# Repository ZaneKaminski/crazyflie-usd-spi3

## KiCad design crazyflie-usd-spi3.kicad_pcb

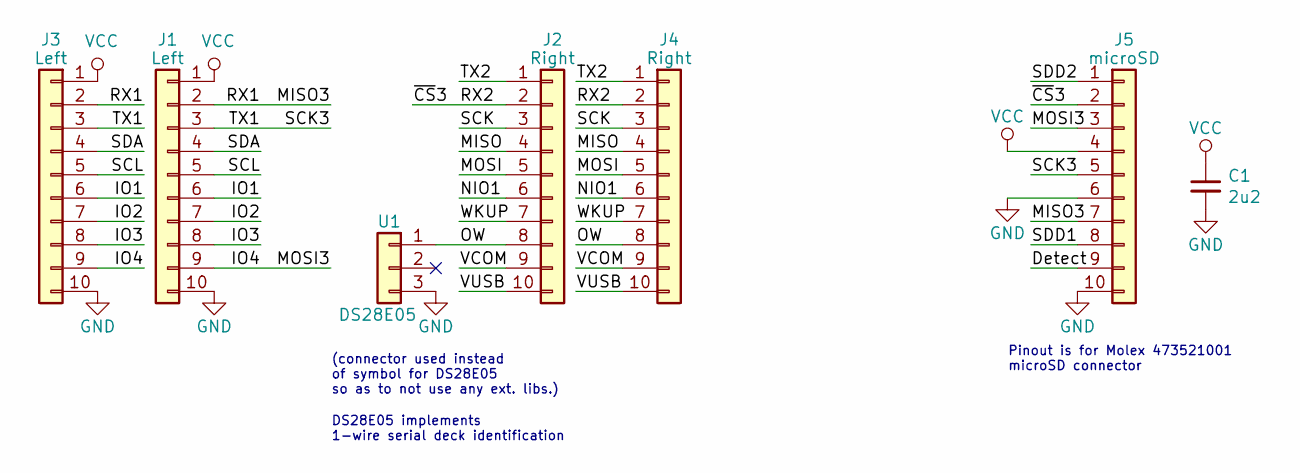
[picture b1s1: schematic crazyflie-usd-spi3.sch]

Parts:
C1: 2u2; C_0805
J1: Left; PinSocket_1x10_P2.00mm_Vertical_SMD_Pin1Left
J2: Right; PinSocket_1x10_P2.00mm_Vertical_SMD_Pin1Right
J3: Left; PinHeader_1x10_P2.00mm_Vertical
J4: Right; PinHeader_1x10_P2.00mm_Vertical
J5: microSD; Molex_473521001_microSD
U1: DS28E05; SOT-23

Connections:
/Detect: J5.9
/IO1: J1.6, J3.6
/IO2: J1.7, J3.7
/IO3: J1.8, J3.8
/IO4: J1.9, J3.9, J5.3
/MISO: J2.4, J4.4
/MISO3: J1.2, J3.2, J5.7
/MOSI: J2.5, J4.5
/NIO1: J2.6, J4.6
/OW: J2.8, J4.8, U1.1
/RX2: J2.2, J4.2, J5.2
/SCK: J2.3, J4.3
/SCK3: J1.3, J3.3, J5.5
/SCL: J1.5, J3.5
/SDA: J1.4, J3.4
/SDD1: J5.8
/SDD2: J5.1
/TX2: J2.1, J4.1
/VCOM: J2.9, J4.9
/VUSB: J2.10, J4.10
/WKUP: J2.7, J4.7
GND: C1.2, J1.10, J3.10, J5.6, J5.10, U1.3
VCC: C1.1, J1.1, J3.1, J5.4

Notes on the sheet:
Pinout is for Molex 473521001 microSD connector
DS28E05 implements 1-wire serial deck identification
(connector used instead of symbol for DS28E05 so as to not use any ext. libs.)

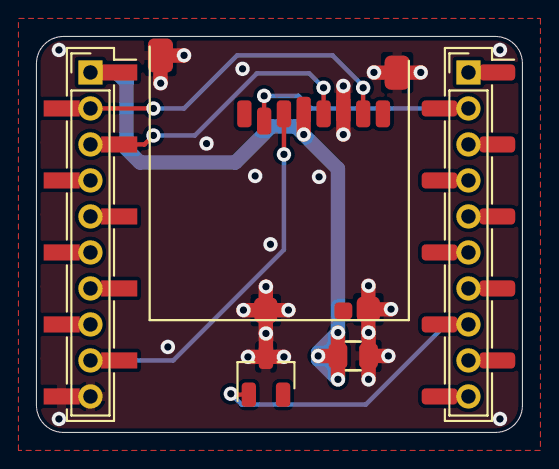
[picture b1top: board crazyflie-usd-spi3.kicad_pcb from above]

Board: 2 copper layers, 27.0 x 22.0 mm, 7 parts (0 on the bottom side), 20 nets.

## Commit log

2020-03-27 Finished board?
2020-05-14 As sent to JLCPCB
2020-05-15 As sent to JLCPCB? but actually exported?
